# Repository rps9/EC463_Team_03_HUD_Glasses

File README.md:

# Team 3: HUDini

<p align="center">
This is our team
</p>

## Description
We’re building a live translation device that utilizes a microphone and Head-Up Display (HUD) to turn spoken foreign speech into real-time English captions, all housed in a pair of glasses. A companion app learns user style to suggest relevant replies, which are displayed phonetically for easy pronunciation on the HUD.

## Objectives
The HUDini will enable fluid two-way conversation, accelerate language learning, and generally facilitate communication across various languages. Planned deliverables: working product with live speech translation and response suggestion.

## Team links
- [Team Google Drive](https://drive.google.com/drive/folders/1bL06aGVt6rRM7B_IEEJm4XVPyzq0NuTs)

## Course links
- [ECE Senior Design Piazza Site](https://piazza.com/bu/fall2025/ec463/home)
- [Blackboard](http://learn.bu.edu/)

## Optional features links
- [Team Jira](https://hudinihudini.atlassian.net/jira/software/projects/SCRUM/boards/1/backlog?atlOrigin=eyJpIjoiNmE5ZTc0OWFmNWZhNGU0NGFmZTQ0ZDc3ZjNkZWU4YzciLCJwIjoiaiJ9&selectedIssue=SCRUM-3)

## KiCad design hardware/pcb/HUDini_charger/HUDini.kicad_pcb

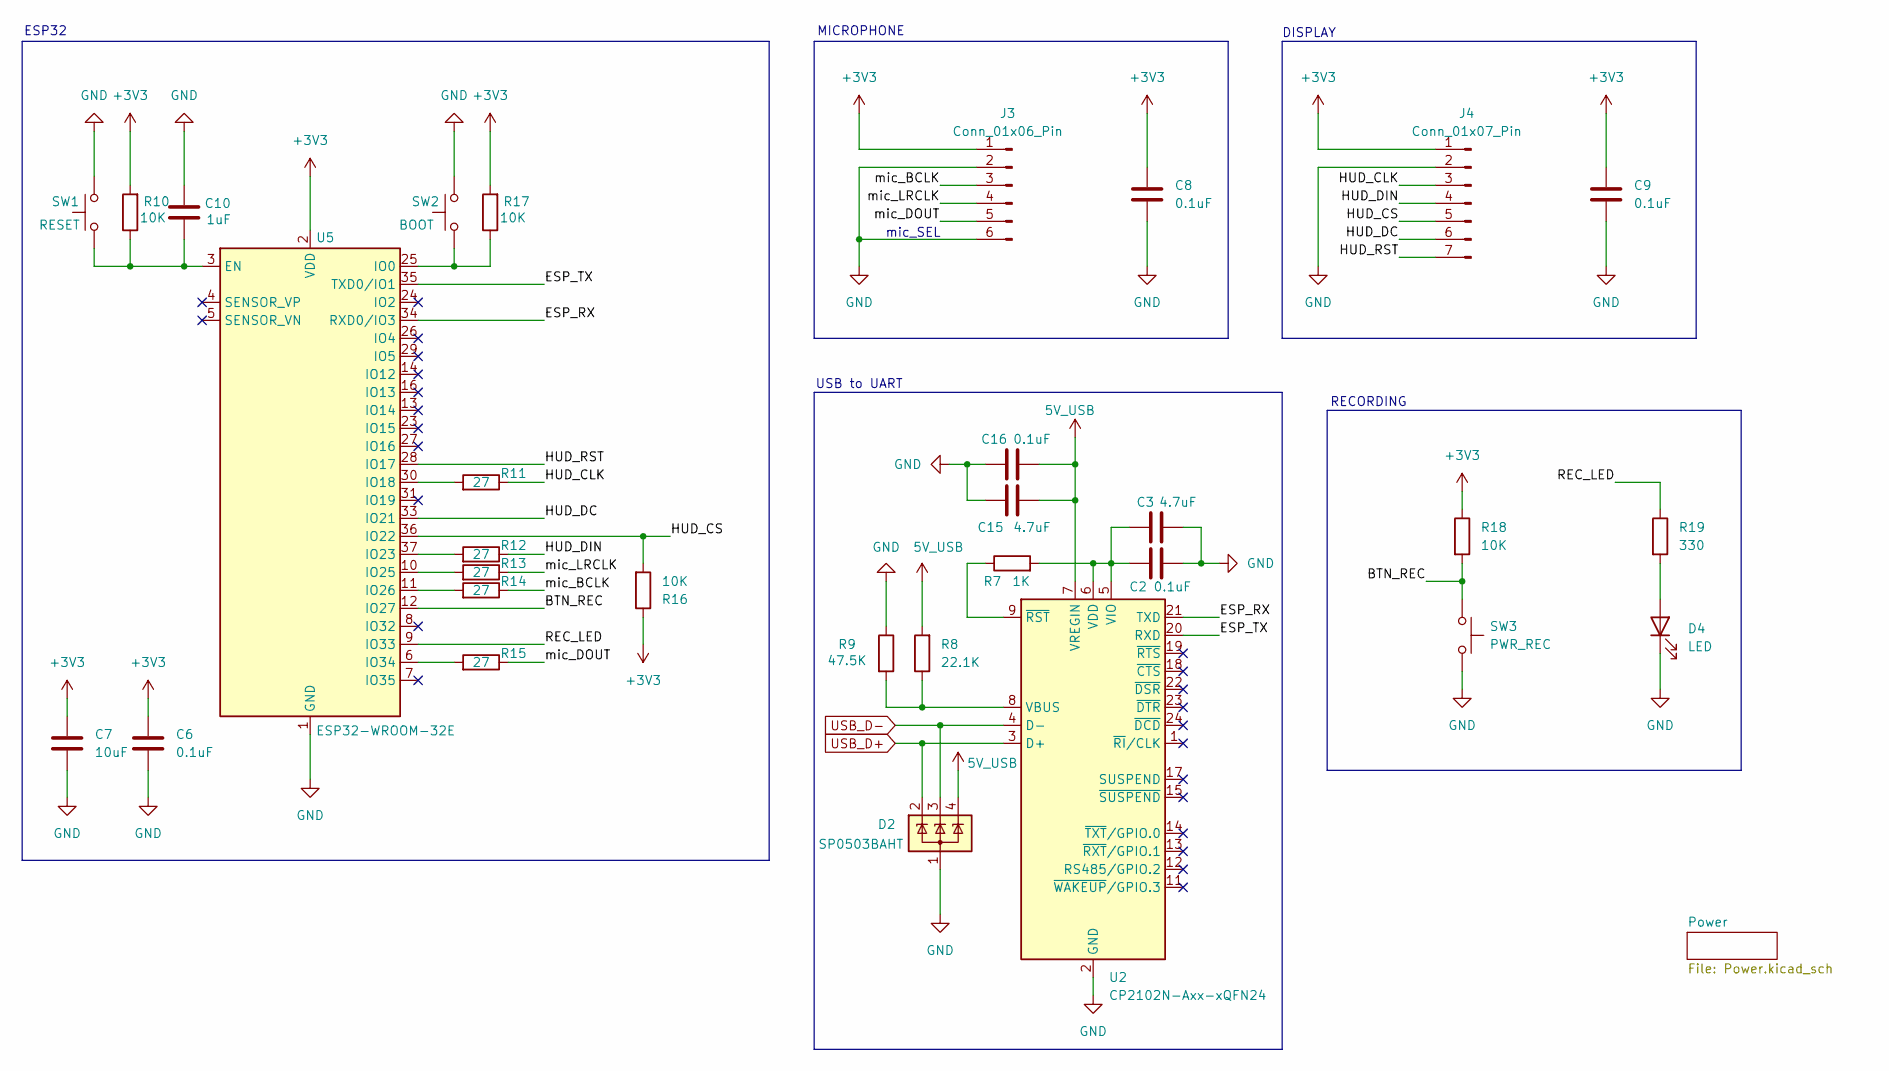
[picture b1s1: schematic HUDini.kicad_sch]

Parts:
C2, C6, C8, C9, C16: 0.1uF; C_0603_1608Metric_Pad1.08x0.95mm_HandSolder
C3, C15: 4.7uF; C_0603_1608Metric_Pad1.08x0.95mm_HandSolder
C7: 10uF; C_0603_1608Metric_Pad1.08x0.95mm_HandSolder
C10: 1uF; C_0603_1608Metric_Pad1.08x0.95mm_HandSolder
D2: SP0503BAHT; SOT-143
D4: LED; LED_0603_1608Metric_Pad1.05x0.95mm_HandSolder
J3: Conn_01x06_Pin; SolderWire-0.15sqmm_1x06_P4mm_D0.5mm_OD1.5mm
J4: Conn_01x07_Pin; PinHeader_1x07_P2.00mm_Horizontal
R7: 1K; R_0603_1608Metric_Pad0.98x0.95mm_HandSolder
R8: 22.1K; R_0603_1608Metric_Pad0.98x0.95mm_HandSolder
R9: 47.5K; R_0603_1608Metric_Pad0.98x0.95mm_HandSolder
R10, R16, R17, R18: 10K; R_0603_1608Metric_Pad0.98x0.95mm_HandSolder
R11, R12, R13, R14, R15: 27; R_0603_1608Metric_Pad0.98x0.95mm_HandSolder
R19: 330; R_0603_1608Metric_Pad0.98x0.95mm_HandSolder
SW1: RESET; SW_SPST_PTS810
SW2: BOOT; SW_SPST_PTS810
SW3: PWR_REC; SW_SPST_PTS645Sx43SMTR92
U2: CP2102N-Axx-xQFN24; QFN-24-1EP_4x4mm_P0.5mm_EP2.6x2.6mm
U5: ESP32-WROOM-32E

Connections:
5V_USB: C15.1, C16.1, D2.4 (K), R8.2, U2.7 (VREGIN); also elsewhere on the board
+3V3: C6.1, C7.1, C8.1, C9.1, J3.1, J4.1, R10.2, R16.1, R17.2, R18.1, U5.2 (VDD); also elsewhere on the board
/BTN_REC: R18.2, SW3.1, U5.12 (IO27)
/ESP_RX: U2.21 (TXD), U5.34 (RXD0/IO3)
/ESP_TX: U2.20 (RXD), U5.35 (TXD0/IO1)
/HUD_CLK: J4.3, R11.1
/HUD_CS: J4.5, R16.2, U5.36 (IO22)
/HUD_DC: J4.6, U5.33 (IO21)
/HUD_DIN: J4.4, R12.1
/HUD_RST: J4.7, U5.28 (IO17)
/REC_LED: R19.1, U5.9 (IO33)
/mic_BCLK: J3.3, R14.1
/mic_DOUT: J3.5, R15.1
/mic_LRCLK: J3.4, R13.1
GND: C2.2, C3.2, C6.2, C7.2, C8.2, C9.2, C10.2, C15.2, C16.2, D2.1 (A), D4.1 (K), J3.2, J3.6, J4.2, R9.1, SW1.2, SW2.2, SW3.2, U2.2 (GND), U2.25 (GND), U5.1 (GND), U5.15 (GND), U5.38 (GND), U5.39 (GND); also elsewhere on the board
unnamed: D4.2 (A), R19.2
unnamed: R8.1, R9.2, U2.8 (VBUS)
unnamed: C2.1, C3.1, R7.2, U2.5 (VIO), U2.6 (VDD)
unnamed: R7.1, U2.9 (~RST)
unnamed: C10.1, R10.1, SW1.1, U5.3 (EN)
unnamed: R17.1, SW2.1, U5.25 (IO0)
unnamed: R11.2, U5.30 (IO18)
unnamed: R12.2, U5.37 (IO23)
unnamed: R13.2, U5.10 (IO25)
unnamed: R14.2, U5.11 (IO26)
unnamed: R15.2, U5.6 (IO34)
USB_D+: D2.2 (K), U2.3 (D+); also elsewhere on the board
USB_D-: D2.3 (K), U2.4 (D-); also elsewhere on the board

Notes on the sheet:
RECORDING
USB to UART
MICROPHONE
ESP32
DISPLAY
mic_SEL

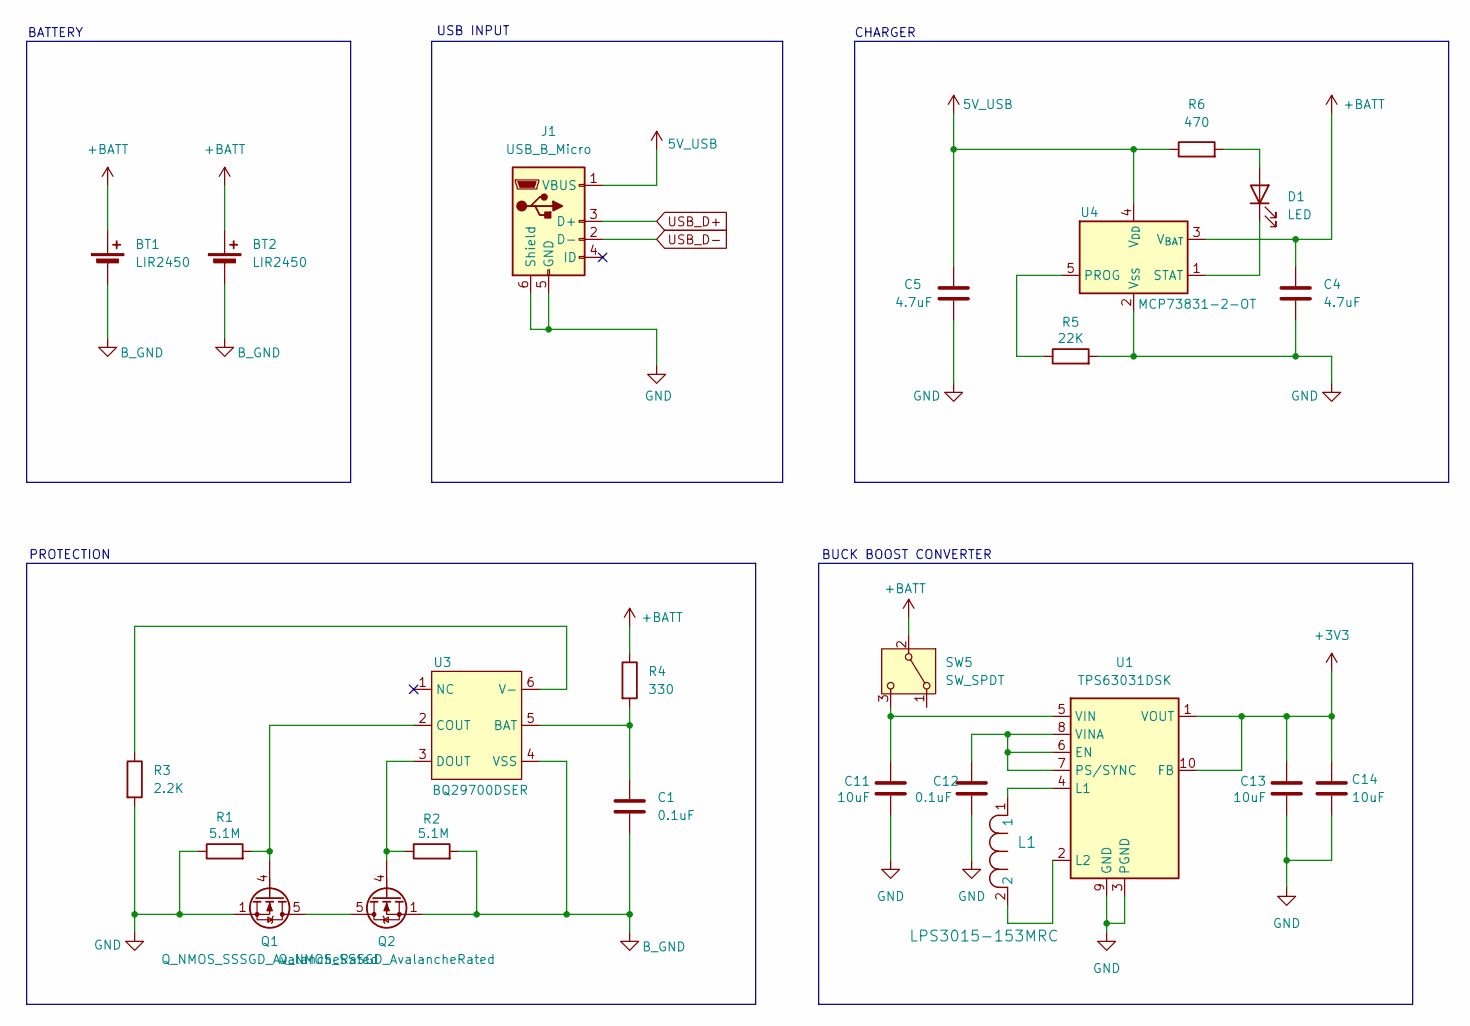
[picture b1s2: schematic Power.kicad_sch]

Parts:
BT1, BT2: LIR2450; SolderWire-0.15sqmm_1x02_P4mm_D0.5mm_OD1.5mm
C1, C12: 0.1uF; C_0603_1608Metric_Pad1.08x0.95mm_HandSolder
C4, C5: 4.7uF; C_0603_1608Metric_Pad1.08x0.95mm_HandSolder
C11, C13, C14: 10uF; C_0603_1608Metric_Pad1.08x0.95mm_HandSolder
D1: LED; LED_0603_1608Metric_Pad1.05x0.95mm_HandSolder
J1: USB_B_Micro; USB_Micro-B_Amphenol_10103594-0001LF_Horizontal
L1: LPS3015-153MRC; LPS3015
Q1, Q2: Q_NMOS_SSSGD_AvalancheRated; VSON-8_3.3x3.3mm_P0.65mm_NexFET
R1, R2: 5.1M; R_0603_1608Metric_Pad0.98x0.95mm_HandSolder
R3: 2.2K; R_0603_1608Metric_Pad0.98x0.95mm_HandSolder
R4: 330; R_0603_1608Metric_Pad0.98x0.95mm_HandSolder
R5: 22K; R_0603_1608Metric_Pad0.98x0.95mm_HandSolder
R6: 470; R_0603_1608Metric_Pad0.98x0.95mm_HandSolder
SW5: SW_SPDT; SW_E-Switch_EG1224_SPDT_Angled
U1: TPS63031DSK; WSON-10-1EP_2.5x2.5mm_P0.5mm_EP1.2x2mm
U3: BQ29700DSER; WSON-6_1.5x1.5mm_P0.5mm
U4: MCP73831-2-OT; SOT-23-5

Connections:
5V_USB: C5.1, J1.1 (VBUS), R6.1, U4.4 (V_{DD}); also elsewhere on the board
+3V3: C13.1, C14.1, U1.1 (VOUT), U1.10 (FB); also elsewhere on the board
+BATT: BT1.1 (+), BT2.1 (+), C4.1, R4.1, SW5.2 (B), U4.3 (V_{BAT})
B_GND: BT1.2 (-), BT2.2 (-), C1.2, Q2.1 (S), Q2.2 (S), Q2.3 (S), R2.2, U3.4 (VSS)
GND: C4.2, C5.2, C11.2, C12.1, C13.2, C14.2, J1.5 (GND), J1.6 (Shield), Q1.1 (S), Q1.2 (S), Q1.3 (S), R1.1, R3.2, R5.2, U1.3 (PGND), U1.9 (GND), U1.11 (PGND), U4.2 (V_{SS}); also elsewhere on the board
unnamed: D1.2 (A), R6.2
unnamed: D1.1 (K), U4.1 (STAT)
unnamed: Q1.5 (D), Q2.5 (D)
unnamed: Q1.4 (G), R1.2, U3.2 (COUT)
unnamed: Q2.4 (G), R2.1, U3.3 (DOUT)
unnamed: C11.1, SW5.3 (C), U1.5 (VIN)
unnamed: C12.2, U1.6 (EN), U1.7 (PS/SYNC), U1.8 (VINA)
unnamed: L1.1, U1.4 (L1)
unnamed: L1.2, U1.2 (L2)
unnamed: C1.1, R4.2, U3.5 (BAT)
unnamed: R3.1, U3.6 (V-)
unnamed: R5.1, U4.5 (PROG)
USB_D+: J1.3 (D+); also elsewhere on the board
USB_D-: J1.2 (D-); also elsewhere on the board

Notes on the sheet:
CHARGER
BUCK BOOST CONVERTER
PROTECTION
USB INPUT
BATTERY

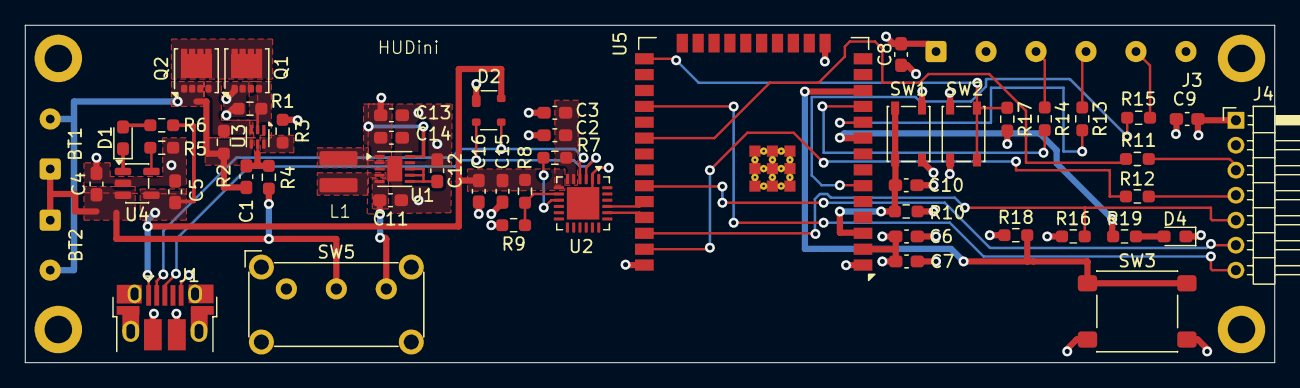
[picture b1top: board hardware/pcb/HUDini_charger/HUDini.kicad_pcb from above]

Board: 4 copper layers, 100.0 x 27.0 mm, 55 parts (0 on the bottom side), 42 nets.

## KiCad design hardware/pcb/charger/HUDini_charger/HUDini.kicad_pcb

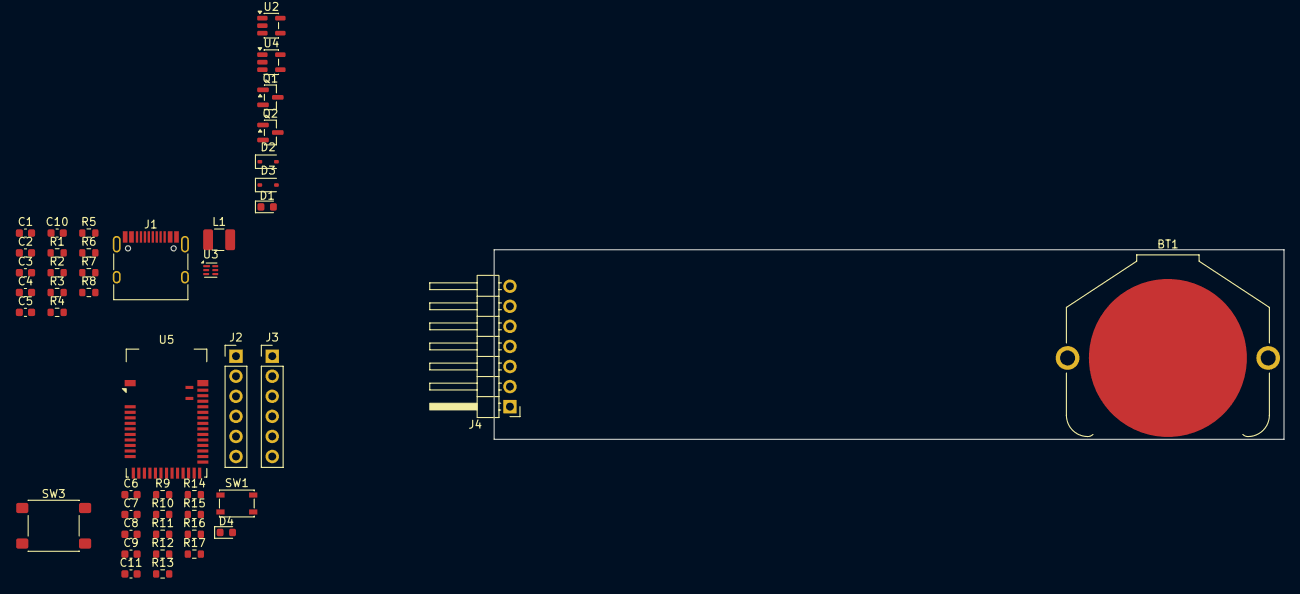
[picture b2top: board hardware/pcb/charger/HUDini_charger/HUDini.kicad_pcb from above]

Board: 2 copper layers, 100.0 x 24.0 mm, 46 parts (0 on the bottom side), 38 nets, no tracks yet.

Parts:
BT1: LIR2450; BatteryHolder_Keystone_3009_1x2450
C1: 22uF; C_0603_1608Metric
C2: 10uF; C_0603_1608Metric
C3, C6, C8, C9: 0.1uF; C_0603_1608Metric
C4, C5: 4.7uF; C_0603_1608Metric
C7, C11: 1uF; C_0603_1608Metric
C10: 100uF; C_0603_1608Metric
D1, D4: LED; LED_0603_1608Metric
D2, D3: D_Zener_Filled; D_SOD-323
J1: USB_C_Receptacle_PowerOnly_6P; USB_C_Receptacle_HRO_TYPE-C-31-M-12
J2, J3: Conn_01x06_Pin; PinHeader_1x06_P2.54mm_Vertical
J4: Conn_01x07_Pin; PinHeader_1x07_P2.54mm_Horizontal
L1: 2.2uH; L_1210_3225Metric
Q1: CHG (GDS); SOT-23
Q2: DSG (GDS); SOT-23
R1, R2: 5.1M; R_0603_1608Metric
R3: 2.2K; R_0603_1608Metric
R4, R11: 330; R_0603_1608Metric
R5: 22K; R_0603_1608Metric
R6: 470; R_0603_1608Metric
R7, R8: 5.1K; R_0603_1608Metric
R9: 100K; R_0603_1608Metric
R10, R12: 10K; R_0603_1608Metric
R13, R14, R15, R16, R17: 27; R_0603_1608Metric
SW1: RESET; SW_SPST_PTS810
SW3: PWR_REC; SW_SPST_PTS645Sx43SMTR92
U2: LM3671; SOT-23-5
U3: BQ29700DSER; WSON-6_1.5x1.5mm_P0.5mm
U4: MCP73831-2-OT; SOT-23-5
U5: MDBT42Q-512K; Raytac_MDBT42Q

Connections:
5V_USB: C5.1, D2.2 (A), J1.A9 (VBUS), J1.B9 (VBUS), R6.1, U4.4 (V_{DD})
+3V3: C2.1, C6.1, C7.1, C8.1, C9.1, J2.1, J3.1, J4.1, L1.2, R9.2, R10.1, R12.1, U2.4 (FB), U5.11 (VDD)
/BTN_PWRREC: R10.2, SW3.1, U5.41 (P0.23)
/HUD_CLK: J4.3, R13.1
/HUD_CS: J4.5, R12.2, U5.31 (P0.17)
/HUD_DC: J4.6, U5.33 (P0.19)
/HUD_DIN: J4.4, R14.1
/HUD_RST: J4.7, U5.38 (P0.22)
/REC_LED: R11.1, U5.40 (P0.24)
/RESET: J2.5, R9.1, SW1.1, U5.35 (P0.21/~RESET)
/SWDCLK: J2.3, U5.36 (SWDCLK)
/SWDIO: J2.4, U5.37 (SWDIO)
/UART_TX: J2.6, U5.21 (P0.08)
/mic_BCLK: J3.3, R15.1
/mic_DOUT: J3.5, R17.1
/mic_LRCLK: J3.4, R16.1
B_GND: BT1.2 (-), C3.2, Q2.3 (S), R2.2, U3.4 (VSS)
GND: C1.2, C2.2, C4.2, C5.2, C6.2, C7.2, C8.2, C9.2, C10.2, C11.1, D3.2 (A), D4.1 (K), J1.A12 (GND), J1.B12 (GND), J1.S1 (SHIELD), J2.2, J3.2, J3.6, J4.2, Q1.3 (S), R1.1, R3.2, R5.2, R7.2, R8.2, SW1.2, SW3.2, U2.2 (GND), U4.2 (V_{SS}), U5.1 (GND), U5.12 (GND), U5.24 (GND), U5.39 (GND)
unnamed: D1.2 (A), R6.2
unnamed: D1.1 (K), U4.1 (STAT)
unnamed: D2.1 (K), D3.1 (K)
unnamed: D4.2 (A), R11.2
unnamed: J1.A5 (CC1), R7.1
unnamed: J1.B5 (CC2), R8.1
unnamed: Q1.2 (D), Q2.2 (D)
unnamed: Q1.1 (G), R1.2, U3.2 (COUT)
unnamed: Q2.1 (G), R2.1, U3.3 (DOUT)
unnamed: L1.1, U2.5 (SW)
unnamed: C3.1, R4.2, U3.5 (BAT)
unnamed: R3.1, U3.6 (V-)
unnamed: R5.1, U4.5 (PROG)
unnamed: C11.2, U5.9 (DEC4)
unnamed: R15.2, U5.25 (P0.11)
unnamed: R16.2, U5.26 (P0.12)
unnamed: R17.2, U5.27 (P0.13)
unnamed: R13.2, U5.30 (TRACEDATA1/P0.16)
unnamed: R14.2, U5.29 (TRACEDATA2/P0.15)
VBAT: BT1.1 (+), C1.1, C4.1, C10.1, R4.1, U2.1 (VIN), U2.3 (EN), U4.3 (V_{BAT})

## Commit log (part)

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2025-09-04 Formatting changes
2025-09-06 Adding team google drive
2025-09-10 adding team picture
2025-09-23 Fix Google Drive link in README.md
2025-10-16 demo translation stuff
2025-10-16 got the UI working with basic FastAPI server
2025-10-21 adding phonetic functionality
2025-10-21 updating UI
2025-10-31 making a branch for the app to keep all of the code on our team repo
2025-10-31 testing
2025-10-31 Revert "Fix Google Drive link in README.md"
    This reverts commit 77d3d027a72a8f062d34c8084bce9757dea9053f.
2025-11-04 update gitignore
2025-11-04 creating phonemizer module
2025-11-04 changing open ai key since I just published it
2025-11-04 update gitignore again
2025-11-04 Changing name to be more general
2025-11-05 adding testing fucntions
2025-11-06 Added translation module
2025-11-06 Updated translation component testing.
2025-11-06 Translation Component Testing now includes an extra test case testing COMET accuracy.
2025-11-06 Add goodbye to dev_set.csv
2025-11-06 Rename Test File
2025-11-07 demo upload
2025-11-13 Added translation function and corresponding tests. Also added new app icon.
2025-11-13 Added COMET score for evaluation purposes.
2025-11-13 updating gitignore
2025-11-13 getting rid of unneeded files
2025-11-13 changing minimum deployment and gitignore
2025-11-14 updating the help prompts
2025-11-14 trying to get bluetooth testing working
2025-11-14 Creating bluetooth display helper
    Use this to demo bluetooth capabilities.
2025-11-16 quick changes
2025-11-16 Combined the two components of the app into a single app.
2025-11-17 ADDED SOME STUFF
2025-11-17 adding changes for demo
2025-11-17 stop tracking this
2025-11-18 adding some changes for the demo
2025-11-20 making the HUD mode better
2025-12-08 demo stuff
2026-01-29 cleaning up main branch
2026-01-29 adding team jira
2026-02-03 adding hardware folder
2026-02-03 Created Purchased Components
2026-02-05 google auth demo
2026-02-05 Basic skeleton for signing in
2026-02-09 finishing clean up
2026-02-11 getting google auth to work with the API
2026-02-11 getting google auth to work completely
2026-02-11 adding all changes
2026-02-11 starting reset password implementation
2026-02-11 Added Login Tab and slightly changed sign in
2026-02-12 taking it out of testing mode
2026-02-14 changing the api to run on ec2 instance
2026-02-14 leftover commit
2026-02-18 adding mic code
2026-02-18 testing BLE to app for audio
2026-02-20 getting the bluetooth mic to work in app
2026-02-26 Changed API address to rps9.net
2026-03-04 Finish feature updates
2026-03-04 Reorganized Repo Structure - more Folders to keep things organized
2026-03-04 Changed Configurations
2026-03-05 for demo
2026-03-05 feature demo II
2026-03-05 changes for demo
2026-03-24 adding support for new chip
2026-03-28 HUD live: wire mic transcription and translation; add Language tab
    - Replace HUDLiveView demo timeline with TranscriptionManager pipeline;
    show translated renderedText on the HUD with character limit.
    - Request speech permissions on appear; surface statusMessage.
    - Debounce OpenAI suggestion refresh in the view (450ms).
    - Add LanguageView for iOS 26 Translation language packs; include related
    tab, translation options, and companion UI updates.
2026-03-28 google auth and bluetooth stuff
2026-03-28 changing sign in flow
2026-03-28 Changes to the UI
2026-03-28 getting rid of mangum
2026-03-28 Moved Views around for better UI
2026-03-28 adding google logo
2026-03-28 complete UI change
2026-03-28 Edits
2026-03-28 ui fixes
2026-03-28 Suggestion Form
2026-03-28 Account Settings View
2026-03-28 edit
2026-03-28 changing api and some ui
2026-03-28 Google Photo Stuff
2026-03-28 Bug Fix
2026-03-29 Created Folder for PCB Files
2026-03-29 Created README.md for PCB
2026-03-29 Deleted file
2026-03-29 Created charger file
2026-03-29 Added Charger Schematics
2026-03-29 Added Charger Files
2026-03-31 display working
2026-03-31 frame ideas
2026-04-02 phonemizer prototype
2026-04-02 more phonemizer stuff
2026-04-04 getting demo firmware working with mic and display
2026-04-05 frame stuff kind of working
2026-04-07 updates to frame
2026-04-07 improvements to the frame code
2026-04-08 glasses working better but mic still shuts off randomly
2026-04-08 translation working much better
2026-04-08 major bug fixes and refactoring
2026-04-09 Improvement to translation
2026-04-09 finding the bottleneck
2026-04-09 adding batching to increase throughput
2026-04-09 suggestion changes
2026-04-09 mic quality pretty good
2026-04-09 changing mic and tap implementation
2026-04-13 Updated PCB Files
2026-04-15 new files
2026-04-16 More Progress
2026-04-17 Some Components Finished Wiring
    Buck-Boost Converter, USB-to-UART, Protection, Charger. Next step is every connection to ESP32
2026-04-20 Updated PCB
2026-04-20 BOM and added datasheet
2026-04-20 Retry
2026-04-23 adding debounce to tap
2026-04-23 ui changes and supporting ESP32
2026-04-23 changing layout some more
2026-04-24 adding schema for reference
2026-04-24 updating schema
2026-04-27 adding apple sign in
2026-04-28 api changes, ui changes, suggestion changes
2026-04-28 changing api logging
2026-04-28 changing logging
2026-04-28 more logging
2026-04-28 changing tokens allowed
2026-04-28 changing suggestion approach
2026-04-28 working with app in the background now
2026-04-29 api changes and app changes
2026-04-29 glasses working better
2026-04-29 working almost perfectly
2026-04-30 moving files
2026-04-30 firmware changes
2026-04-30 enabling apple sign in again
2026-05-01 working well
2026-05-01 done
2026-05-03 final changes
